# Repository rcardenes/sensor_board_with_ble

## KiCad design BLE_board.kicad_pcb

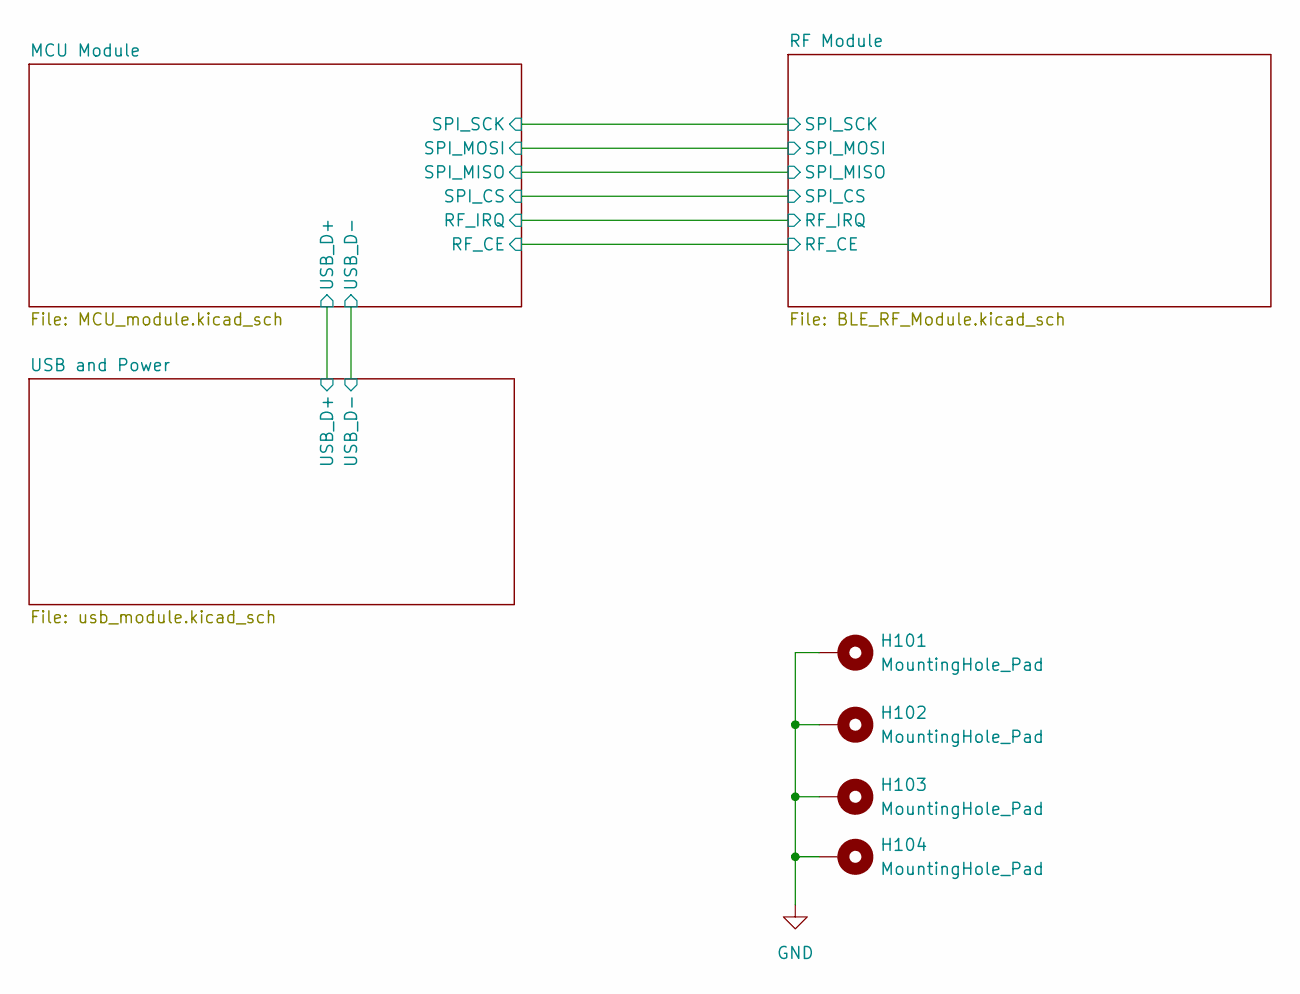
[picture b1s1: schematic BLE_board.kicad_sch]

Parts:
H101, H102, H103, H104: MountingHole_Pad; MountingHole_2.2mm_M2_Pad

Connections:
GND: H101.1, H102.1, H103.1, H104.1; also elsewhere on the board

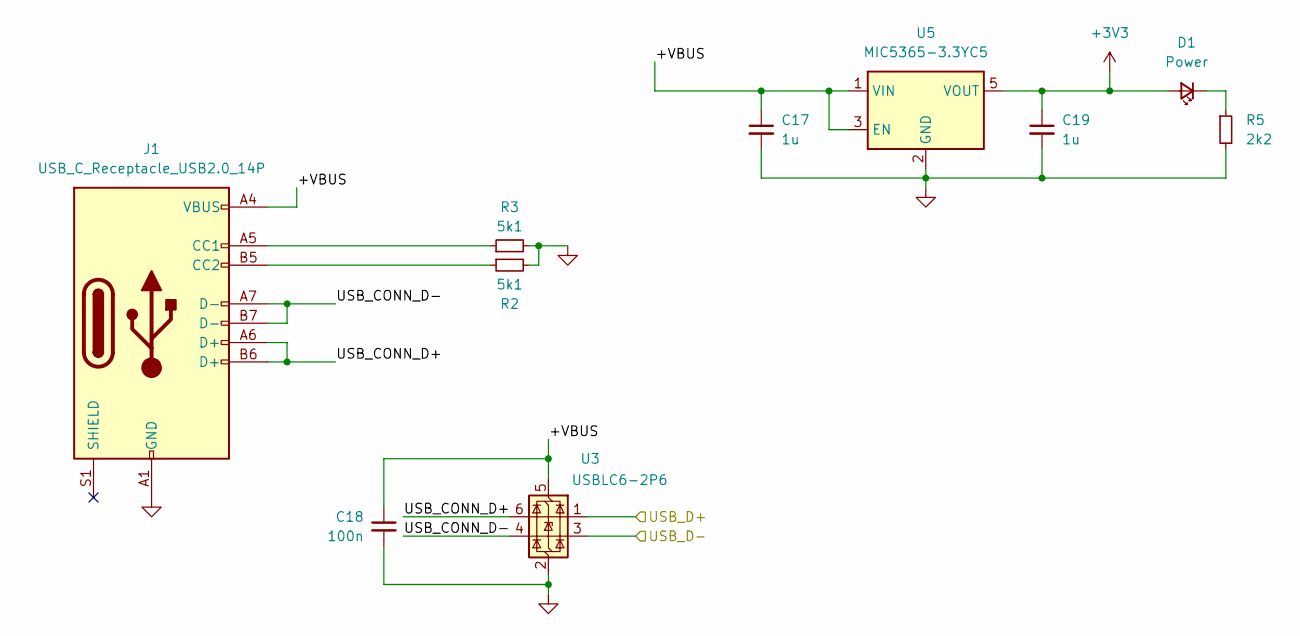
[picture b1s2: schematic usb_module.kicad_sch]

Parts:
C17, C19: 1u; C_0402_1005Metric; MPN C52923
C18: 100n; C_0402_1005Metric; MPN C1525
D1: Power; LED_0603_1608Metric; MPN C2286
J1: USB_C_Receptacle_USB2.0_14P; USB_C_Receptacle_XKB_U262-16XN-4BVC11; MPN C319148; JLCPCB Position Offset 0,1.4605
R2, R3: 5k1; R_0402_1005Metric; MPN C25905
R5: 2k2; R_0402_1005Metric; MPN C25879
U3: USBLC6-2P6; SOT-666; MPN C2827693; JLCPCB Rotation Offset -90
U5: MIC5365-3.3YC5; SOT-353_SC-70-5; MPN C3021118

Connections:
+3V3: C19.1, D1.2 (A), U5.5 (VOUT); also elsewhere on the board
/MCU Module/USB_D+: U3.1 (I/O1); also elsewhere on the board
/MCU Module/USB_D-: U3.3 (I/O2); also elsewhere on the board
/USB and Power/+VBUS: C17.1, C18.1, J1.A4 (VBUS), J1.A9 (VBUS), J1.B4 (VBUS), J1.B9 (VBUS), U3.5 (VBUS), U5.1 (VIN), U5.3 (EN)
/USB and Power/USB_CONN_D+: J1.A6 (D+), J1.B6 (D+), U3.6 (I/O1)
/USB and Power/USB_CONN_D-: J1.A7 (D-), J1.B7 (D-), U3.4 (I/O2)
GND: C17.2, C18.2, C19.2, J1.A1 (GND), J1.A12 (GND), J1.B1 (GND), J1.B12 (GND), R2.2, R3.2, R5.2, U3.2 (GND), U5.2 (GND); also elsewhere on the board
unnamed: D1.1 (K), R5.1
unnamed: J1.A5 (CC1), R3.1
unnamed: J1.B5 (CC2), R2.1

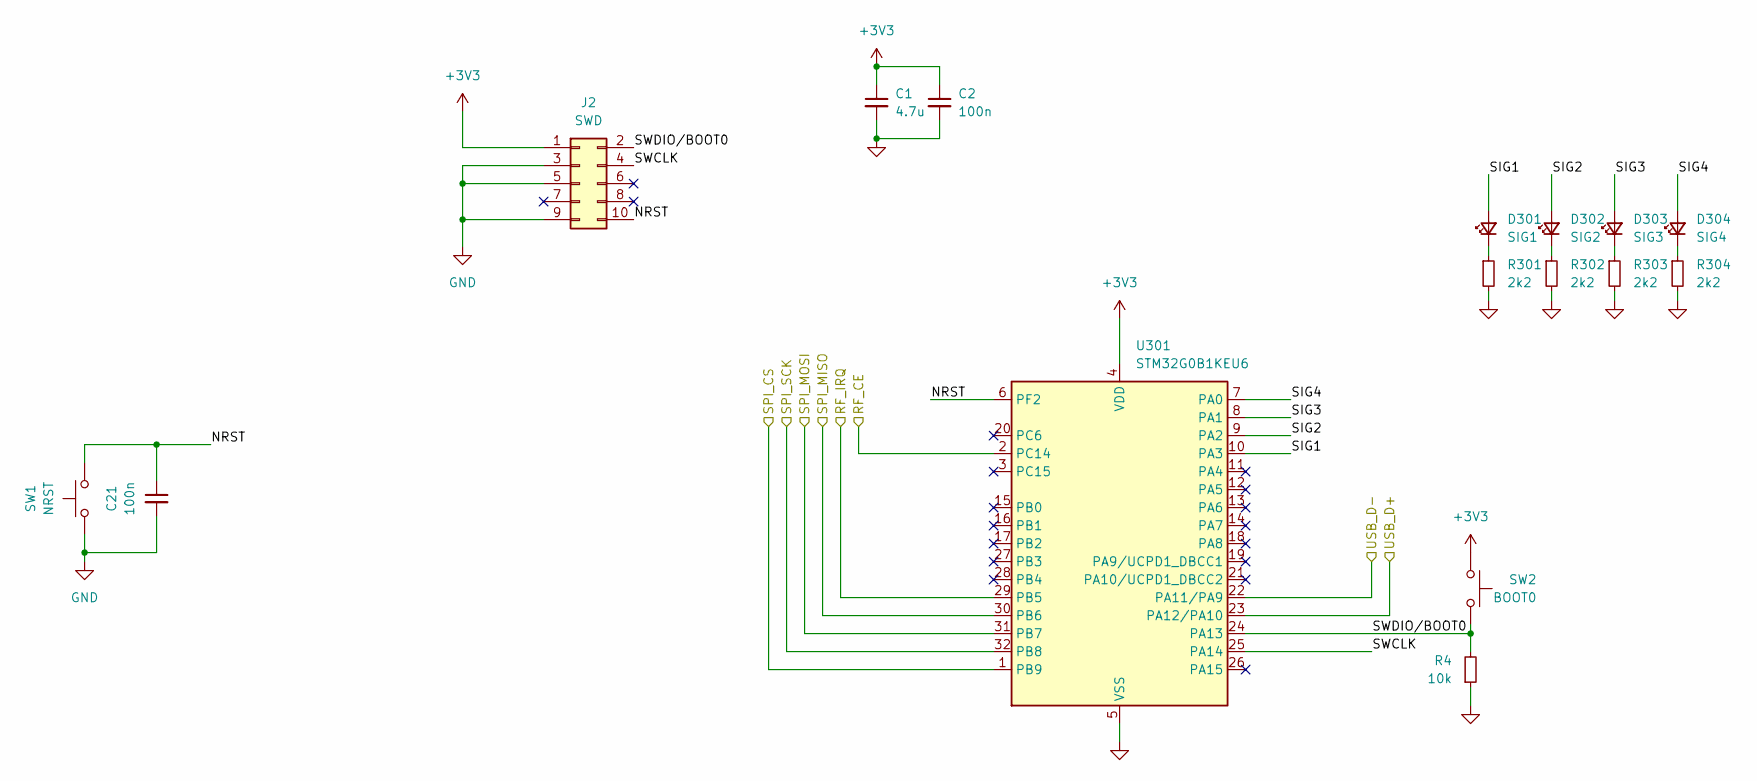
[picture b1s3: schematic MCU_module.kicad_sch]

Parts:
C1: 4.7u; C_0402_1005Metric; MPN C82453
C2, C21: 100n; C_0402_1005Metric; MPN C1525
D301: SIG1; LED_0603_1608Metric; MPN C2286
D302: SIG2; LED_0603_1608Metric; MPN C2286
D303: SIG3; LED_0603_1608Metric; MPN C2286
D304: SIG4; LED_0603_1608Metric; MPN C2286
J2: SWD; PinHeader_2x05_P1.27mm_Vertical_SMD_w_fiducials; MPN C4943297; JLCPCB Rotation Offset -90
R4: 10k; R_0402_1005Metric; MPN C25744
R301, R302, R303, R304: 2k2; R_0402_1005Metric; MPN C25879
SW1: NRST; SW_SPST_B3U-1000P; MPN C231329
SW2: BOOT0; SW_SPST_B3U-1000P; MPN C231329
U301: STM32G0B1KEU6; QFN-32-1EP_5x5mm_P0.5mm_EP3.45x3.45mm

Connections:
+3V3: C1.1, C2.1, J2.1, SW2.2, U301.4 (VDD); also elsewhere on the board
/MCU Module/NRST: C21.1, J2.10, SW1.2, U301.6 (PF2)
/MCU Module/RF_CE: U301.2 (PC14); also elsewhere on the board
/MCU Module/RF_IRQ: U301.29 (PB5); also elsewhere on the board
/MCU Module/SIG1: D301.2 (A), U301.10 (PA3)
/MCU Module/SIG2: D302.2 (A), U301.9 (PA2)
/MCU Module/SIG3: D303.2 (A), U301.8 (PA1)
/MCU Module/SIG4: D304.2 (A), U301.7 (PA0)
/MCU Module/SPI_CS: U301.1 (PB9); also elsewhere on the board
/MCU Module/SPI_MISO: U301.30 (PB6); also elsewhere on the board
/MCU Module/SPI_MOSI: U301.31 (PB7); also elsewhere on the board
/MCU Module/SPI_SCK: U301.32 (PB8); also elsewhere on the board
/MCU Module/SWCLK: J2.4, U301.25 (PA14)
/MCU Module/SWDIO/BOOT0: J2.2, R4.2, SW2.1, U301.24 (PA13)
/MCU Module/USB_D+: U301.23 (PA12/PA10); also elsewhere on the board
/MCU Module/USB_D-: U301.22 (PA11/PA9); also elsewhere on the board
GND: C1.2, C2.2, C21.2, J2.3, J2.5, J2.9, R4.1, R301.2, R302.2, R303.2, R304.2, SW1.1, U301.5 (VSS), U301.33 (VSS); also elsewhere on the board
unnamed: D301.1 (K), R301.1
unnamed: D302.1 (K), R302.1
unnamed: D303.1 (K), R303.1
unnamed: D304.1 (K), R304.1

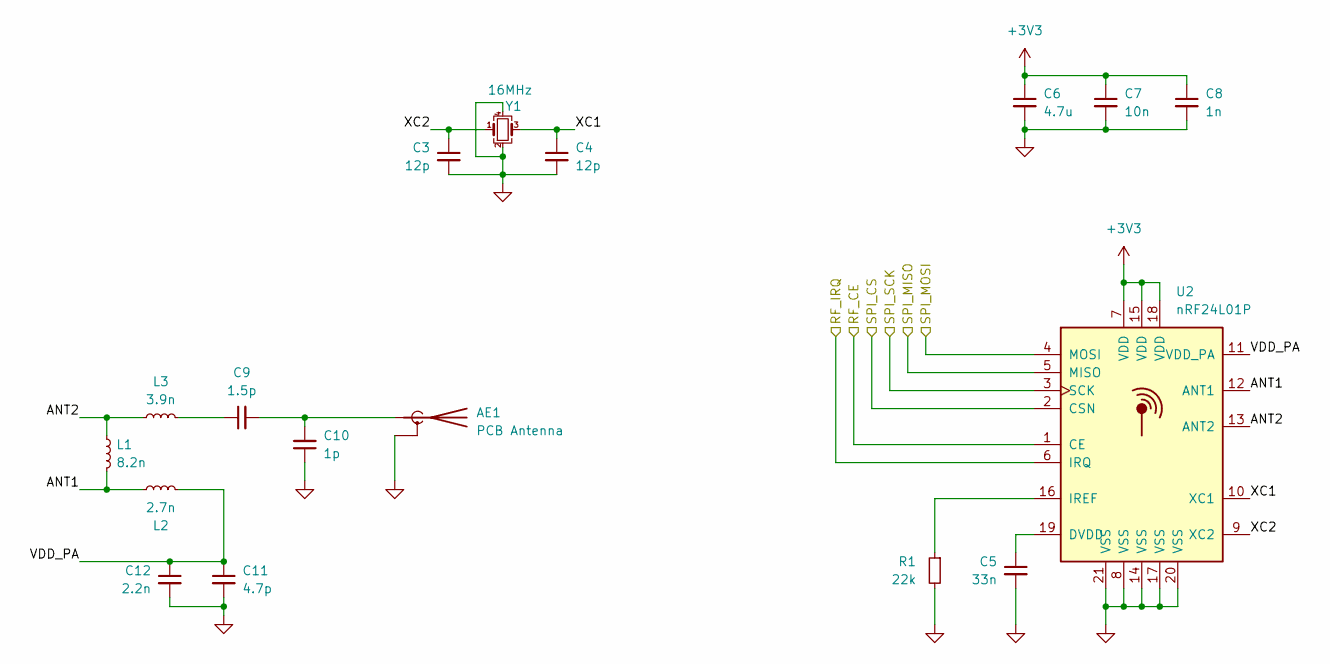
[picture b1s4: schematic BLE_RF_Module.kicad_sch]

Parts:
AE1: PCB Antenna; Texas_SWRA117D_2.4GHz_Right
C3, C4: 12p; C_0402_1005Metric; MPN C1547
C5: 33n; C_0402_1005Metric; MPN C301940
C6: 4.7u; C_0402_1005Metric; MPN C82453
C7: 10n; C_0402_1005Metric; MPN C15195
C8: 1n; C_0402_1005Metric; MPN C1523
C9: 1.5p; C_0402_1005Metric; MPN C1552
C10: 1p; C_0402_1005Metric; MPN C1550
C11: 4.7p; C_0402_1005Metric; MPN C85883
C12: 2.2n; C_0402_1005Metric; MPN C126534
L1: 8.2n; C_0402_1005Metric; MPN C90138
L2: 2.7n; C_0402_1005Metric; MPN C108255
L3: 3.9n; C_0402_1005Metric; MPN C14033
R1: 22k; C_0402_1005Metric; MPN C25768
U2: nRF24L01P; QFN-20-1EP_4x4mm_P0.5mm_EP2.5x2.5mm; MPN C8791; JLCPCB Rotation Offset -90
Y1: 16MHz; Crystal_SMD_3225-4Pin_3.2x2.5mm; MPN C13738

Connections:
+3V3: C6.1, C7.1, C8.1, U2.7 (VDD), U2.15 (VDD), U2.18 (VDD); also elsewhere on the board
/MCU Module/RF_CE: U2.1 (CE); also elsewhere on the board
/MCU Module/RF_IRQ: U2.6 (IRQ); also elsewhere on the board
/MCU Module/SPI_CS: U2.2 (CSN); also elsewhere on the board
/MCU Module/SPI_MISO: U2.5 (MISO); also elsewhere on the board
/MCU Module/SPI_MOSI: U2.4 (MOSI); also elsewhere on the board
/MCU Module/SPI_SCK: U2.3 (SCK); also elsewhere on the board
/RF Module/ANT1: L1.2, L2.2, U2.12 (ANT1)
/RF Module/ANT2: L1.1, L3.1, U2.13 (ANT2)
/RF Module/VDD_PA: C11.1, C12.1, L2.1, U2.11 (VDD_PA)
/RF Module/XC1: C4.1, U2.10 (XC1), Y1.3
/RF Module/XC2: C3.1, U2.9 (XC2), Y1.1
GND: AE1.2 (Shield), C3.2, C4.2, C5.2, C6.2, C7.2, C8.2, C10.1, C11.2, C12.2, R1.2, U2.8 (VSS), U2.14 (VSS), U2.17 (VSS), U2.20 (VSS), U2.21 (VSS), Y1.2, Y1.4; also elsewhere on the board
unnamed: AE1.1 (A), C9.2, C10.2
unnamed: C9.1, L3.2
unnamed: C5.1, U2.19 (DVDD)
unnamed: R1.1, U2.16 (IREF)

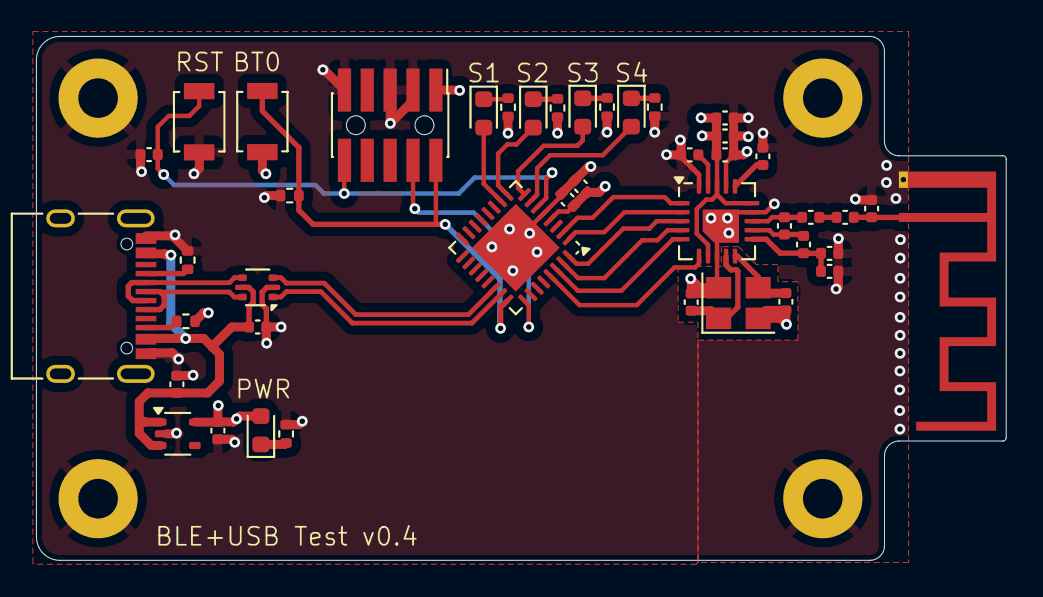
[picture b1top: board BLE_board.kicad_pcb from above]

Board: 4 copper layers, 53.9 x 29.1 mm, 47 parts (0 on the bottom side), 36 nets.

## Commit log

2024-07-26 First basic design
2024-07-27 Easier BOOT0
2024-07-27 Redesigned power supply. First board draft
2024-07-28 First routed board
2024-07-28 BOM assigned
2024-08-19 Minor changes
2024-08-28 Larger dimensions. Include mounting holes. Better antenna feed alignment
2024-08-29 Add signaling LEDs
2024-08-29 Migrated the STM32F0 to an STM32G0B
